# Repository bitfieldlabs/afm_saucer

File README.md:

# :flying_saucer: An RGB Attack from Mars Pinball Saucer PCB Replacement
As the title suggests this is drop in replacement for your Attack from Mars pinball saucer PCB. The large one.

No additional components or connections required!

As a bonus you get nice RGB colors!

See a video of the saucer in action: https://vimeo.com/777834938

## :jigsaw: Required Components

The BOM is [here](https://github.com/bitfieldlabs/afm_saucer/blob/master/afm_saucer_pcb/afm_saucer/afm_saucer_bom.csv).
 
## :page_facing_up: Instructions
Some instructions can be found in the [doc folder](https://github.com/bitfieldlabs/afm_saucer/tree/master/doc).

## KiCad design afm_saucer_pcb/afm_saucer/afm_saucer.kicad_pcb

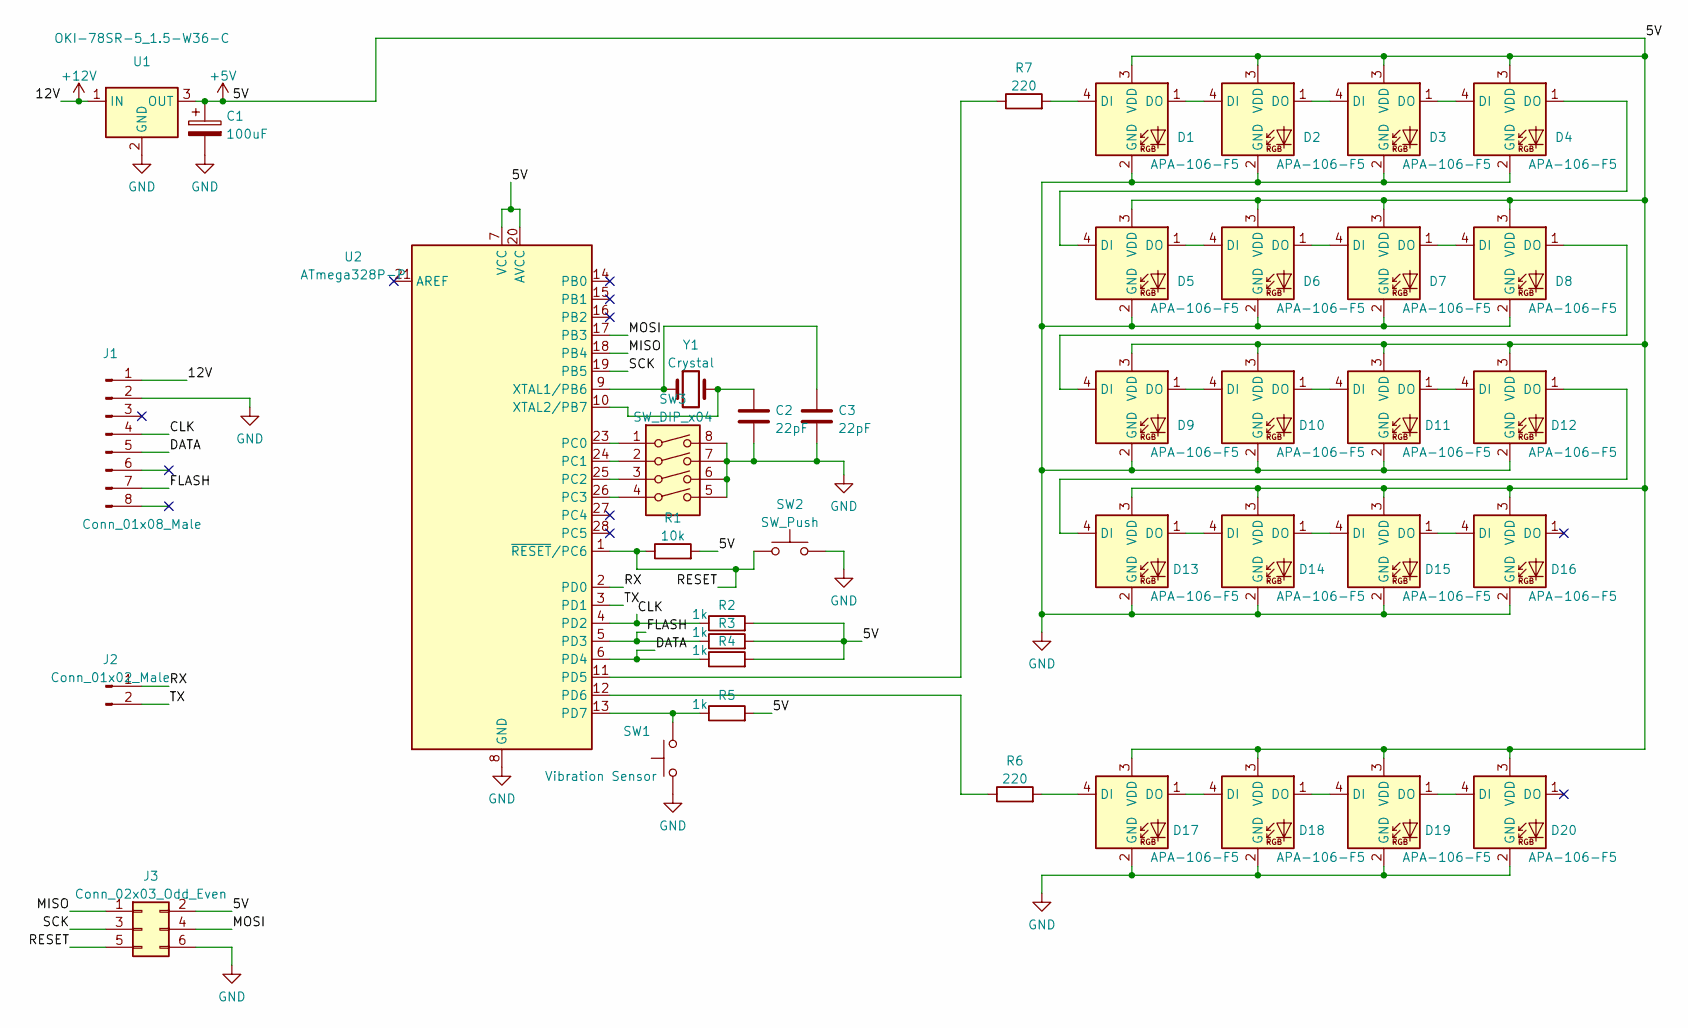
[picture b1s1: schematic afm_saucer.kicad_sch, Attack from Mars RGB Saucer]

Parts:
C1: 100uF; CP_Axial_L21.0mm_D8.0mm_P28.00mm_Horizontal
C2, C3: 22pF; C_Disc_D7.5mm_W5.0mm_P7.50mm
D1, D2, D3, D4, D5, D6, D7, D8, D9, D10, D11, D12, D13, D14, D15, D16, D17, D18, D19, D20: APA-106-F5; LED_D5.0mm-4_RGB
J1: Conn_01x08_Male; PinHeader_1x08_P2.54mm_Horizontal
J2: Conn_01x02_Male; PinHeader_1x02_P2.54mm_Vertical
J3: Conn_02x03_Odd_Even; PinHeader_2x03_P2.54mm_Vertical
R1: 10k; R_Axial_DIN0207_L6.3mm_D2.5mm_P10.16mm_Horizontal
R2, R3, R4, R5: 1k; R_Axial_DIN0207_L6.3mm_D2.5mm_P10.16mm_Horizontal
R6, R7: 220; R_Axial_DIN0207_L6.3mm_D2.5mm_P10.16mm_Horizontal
SW1: Vibration Sensor; PinHeader_1x02_P2.54mm_Horizontal
SW2: SW_Push; SW_PUSH_6mm_H9.5mm
SW3: SW_DIP_x04; SW_DIP_SPSTx04_Slide_9.78x12.34mm_W7.62mm_P2.54mm
U1: OKI-78SR-5_1.5-W36-C; Converter_DCDC_Murata_OKI-78SR_Horizontal
U2: ATmega328P-P; DIP-28_W7.62mm
Y1: Crystal; Resonator-2Pin_W10.0mm_H5.0mm

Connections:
+5V: C1.1, D1.3 (VDD), D2.3 (VDD), D3.3 (VDD), D4.3 (VDD), D5.3 (VDD), D6.3 (VDD), D7.3 (VDD), D8.3 (VDD), D9.3 (VDD), D10.3 (VDD), D11.3 (VDD), D12.3 (VDD), D13.3 (VDD), D14.3 (VDD), D15.3 (VDD), D16.3 (VDD), D17.3 (VDD), D18.3 (VDD), D19.3 (VDD), D20.3 (VDD), J3.2, R1.2, R2.2, R3.2, R4.2, R5.2, U1.3 (OUT), U2.7 (VCC), U2.20 (AVCC)
+12V: J1.1, U1.1 (IN)
/CLK: J1.4, R2.1, U2.4 (PD2)
/DATA: J1.5, R4.1, U2.6 (PD4)
/FLASH: J1.7, R3.1, U2.5 (PD3)
/MISO: J3.1, U2.18 (PB4)
/MOSI: J3.4, U2.17 (PB3)
/RESET: J3.5, R1.1, SW2.1, U2.1 (~RESET/PC6)
/RX: J2.1, U2.2 (PD0)
/SCK: J3.3, U2.19 (PB5)
/TX: J2.2, U2.3 (PD1)
GND: C1.2, C2.2, C3.2, D1.2 (GND), D2.2 (GND), D3.2 (GND), D4.2 (GND), D5.2 (GND), D6.2 (GND), D7.2 (GND), D8.2 (GND), D9.2 (GND), D10.2 (GND), D11.2 (GND), D12.2 (GND), D13.2 (GND), D14.2 (GND), D15.2 (GND), D16.2 (GND), D17.2 (GND), D18.2 (GND), D19.2 (GND), D20.2 (GND), J1.2, J3.6, SW1.1, SW2.2, SW3.5, SW3.6, SW3.7, SW3.8, U1.2 (GND), U2.8 (GND), U2.22 (GND)
unnamed: C2.1, U2.10 (XTAL2/PB7), Y1.2
unnamed: C3.1, U2.9 (XTAL1/PB6), Y1.1
unnamed: D1.1 (DO), D2.4 (DI)
unnamed: D1.4 (DI), R7.2
unnamed: D3.1 (DO), D4.4 (DI)
unnamed: D2.1 (DO), D3.4 (DI)
unnamed: D4.1 (DO), D5.4 (DI)
unnamed: D5.1 (DO), D6.4 (DI)
unnamed: D7.1 (DO), D8.4 (DI)
unnamed: D6.1 (DO), D7.4 (DI)
unnamed: D8.1 (DO), D9.4 (DI)
unnamed: D9.1 (DO), D10.4 (DI)
unnamed: D11.1 (DO), D12.4 (DI)
unnamed: D10.1 (DO), D11.4 (DI)
unnamed: D12.1 (DO), D13.4 (DI)
unnamed: D13.1 (DO), D14.4 (DI)
unnamed: D15.1 (DO), D16.4 (DI)
unnamed: D14.1 (DO), D15.4 (DI)
unnamed: D17.4 (DI), R6.2
unnamed: D18.1 (DO), D19.4 (DI)
unnamed: D17.1 (DO), D18.4 (DI)
unnamed: D19.1 (DO), D20.4 (DI)
unnamed: R5.1, SW1.2, U2.13 (PD7)
unnamed: R6.1, U2.12 (PD6)
unnamed: R7.1, U2.11 (PD5)
unnamed: SW3.1, U2.23 (PC0)
unnamed: SW3.2, U2.24 (PC1)
unnamed: SW3.3, U2.25 (PC2)
unnamed: SW3.4, U2.26 (PC3)

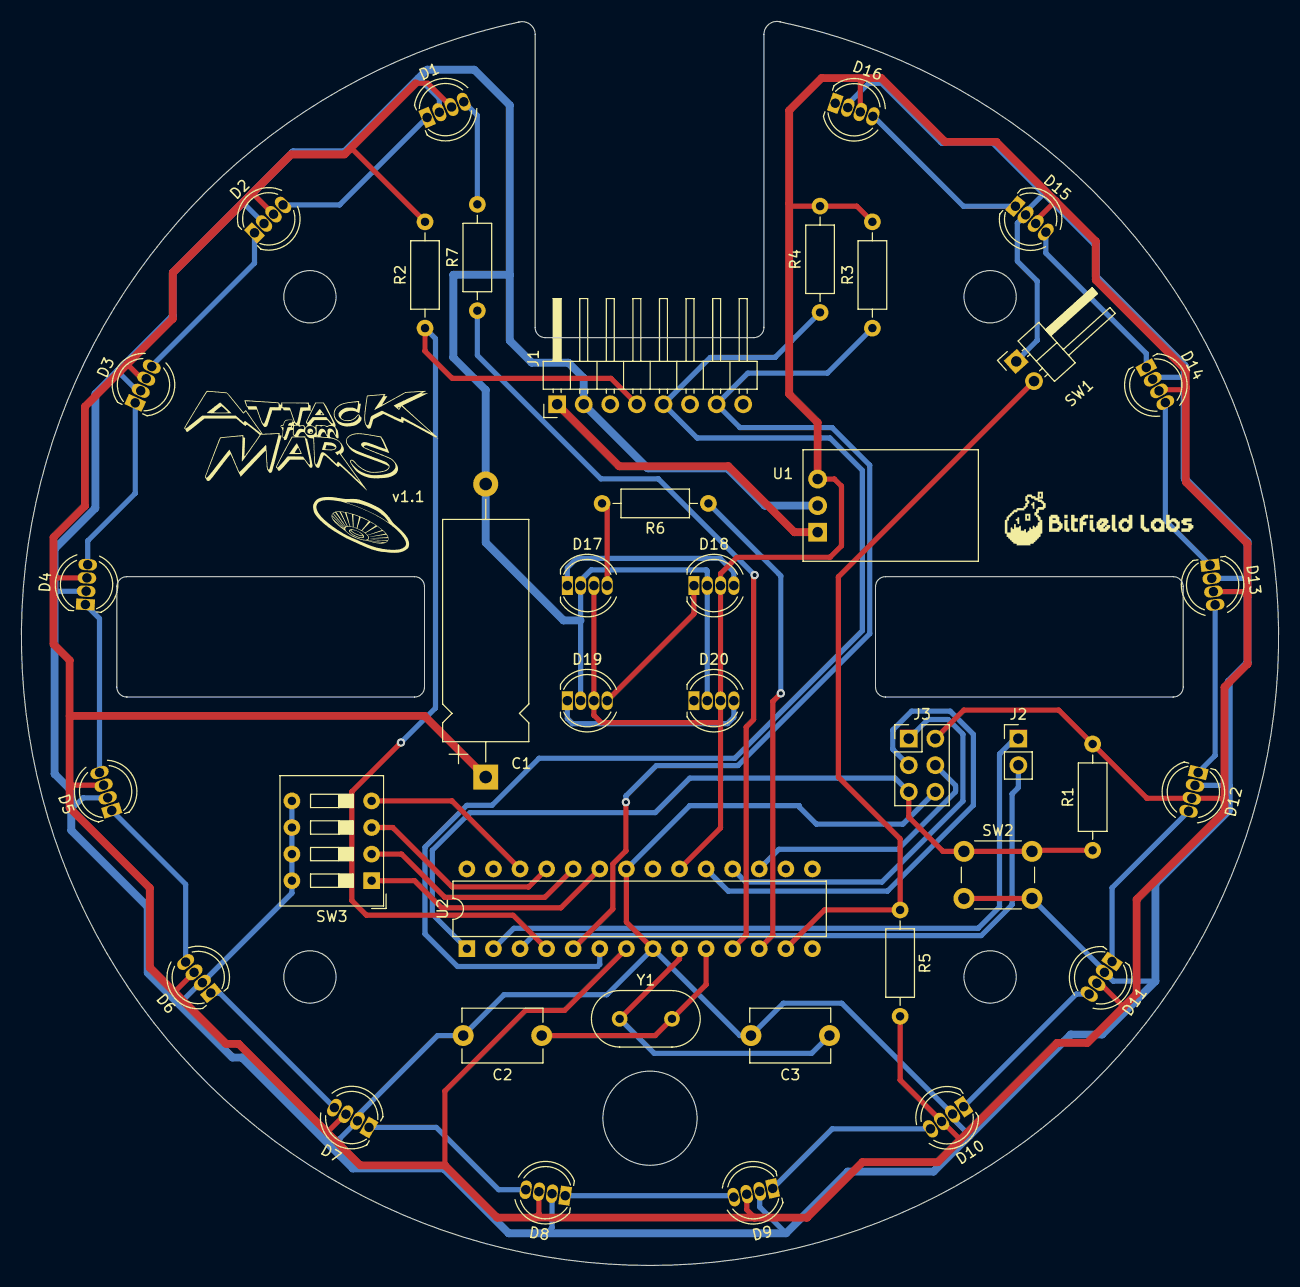
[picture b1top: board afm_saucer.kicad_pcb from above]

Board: 2 copper layers, 120.1 x 118.9 mm, 40 parts (0 on the bottom side), 41 nets.

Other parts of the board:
QR: QRCODE; afm_logo_s

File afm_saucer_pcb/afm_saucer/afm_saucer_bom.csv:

C1,100uF,Capacitor Axial L21.0mm D8.0mm P28.00mm,https://www.mouser.ch/ProductDetail/598-477TTA025M
"C2, C3",22pF,Capacitor Disc D7.5mm W5.0mm P7.50mm,https://www.mouser.ch/ProductDetail/810-CC45SL3JD220JYNA
D1-D20,APA-106-F5,LED D5.0mm RGB,https://www.aliexpress.com/item/32945500333.html?spm=a2g0o.o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
J1,Conn_01x08_Male,PinHeader 1x08 P2.54mm 90deg,https://www.mouser.ch/ProductDetail/538-22-05-7088
J2,Conn_01x02_Male,PinHeader 1x02_P2.54mm Vertical,
J3,Conn_02x03_Odd_Even,PinHeader 2x03 P2.54mm Vertical,
R1,10k,Resistor R_Axial L6.3mm D2.5mm P10.16mm,
"R2, R3, R4, R5",1k,Resistor R_Axial L6.3mm D2.5mm P10.16mm,
"R6, R7",220,Resistor R_Axial L6.3mm D2.5mm P10.16mm,
SW1,Vibration Sensor,Vibration Sensor Medium/Fast,https://www.mouser.ch/ProductDetail/485-2384
SW2,SW_Push,Push Button 6mm H9.5mm,
SW3,SW_DIP_x04,DIP  Switch x04 W7.62mm P2.54mm,
U1,OKI-78SR-5_1.5-W36-C,Converter DCDC_Murata OKI-78SR Horizontal,https://www.mouser.ch/ProductDetail/946-MEZD71202A-G
U2,ATmega328P-P,DIP-28 W7.62mm,
Y1,Crystal,Crystal 2Pin W10.0mm H5.0mm,https://www.mouser.ch/ProductDetail/449-LFXTAL027945BULK

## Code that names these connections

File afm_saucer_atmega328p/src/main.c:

/***********************************************************************
 *    _   _   _             _     __                                           
 *   /_\ | |_| |_ __ _  ___| | __/ _|_ __ ___  _ __ ___   /\/\   __ _ _ __ ___ 
 *  //_\\| __| __/ _` |/ __| |/ / |_| '__/ _ \| '_ ` _ \ /    \ / _` | '__/ __|
 * /  _  \ |_| || (_| | (__|   <|  _| | | (_) | | | | | / /\/\ \ (_| | |  \__ \
 * \_/ \_/\__|\__\__,_|\___|_|\_\_| |_|  \___/|_| |_| |_\/    \/\__,_|_|  |___/
 *
 *                              ____ ____ ___ 
 *                              |--< |__, |==]
 *
 *                      ____ ____ _  _ ____ ____ ____
 *                      ==== |--| |__| |___ |=== |--<
 *
 *  Copyright (c) 2022 bitfield labs
 * 
 ***********************************************************************
 *  This file is part of the Attack from Mars! RGB saucer project:
 *  https://github.com/bitfieldlabs/afm_saucer
 *
 *  The AfM RGB saucer is free software: you can redistribute it and/or
 *  modify it under the terms of the GNU Lesser General Public License as
 *  published by the Free Software Foundation, either version 3 of the
 *  License, or (at your option) any later version.
 *
 *  AfM RGB saucer is distributed in the hope that it will be useful,
 *  but WITHOUT ANY WARRANTY; without even the implied warranty of
 *  MERCHANTABILITY or FITNESS FOR A PARTICULAR PURPOSE.  See the
 *  GNU Lesser General Public License for more details.
 *
 *  You should have received a copy of the GNU Lesser General Public
 *  License along with afterglow.
 *  If not, see <http://www.gnu.org/licenses/>.
 ***********************************************************************/

#include <avr/io.h>
#include <avr/interrupt.h>
#include <avr/eeprom.h>
#include <util/delay.h>
#include <stdlib.h>
#include <stdbool.h>
#include "modes.h"


//------------------------------------------------------------------------------
// definitions

#define LED_UPDATE_INT 20                   // LED update interval [ms]
#define FLASH_CONS_CHECK 1                  // number of consecutive flash line checks in LED_UPDATE_INT interval required for flash triggering


//------------------------------------------------------------------------------
// global variables

static volatile uint16_t svLEDState = 0xffff;    // status for all 16 LEDs
static volatile bool svFlashState = false;       // flasher status
static volatile bool svShakerState = false;      // shaker status
static volatile uint16_t svFlashCounter = 0;     // consecutive passed flash line checks counter


//------------------------------------------------------------------------------
int main(void)
{
    // setup
    DDRD = 0b01100010;                      // all inputs except pins PD1, PD5, PD6
    DDRC = 0b00000000;                      // config DIPs on PC0-PC3
    PORTC |= 0b00001111;                    // enable DIP switch pullups
    EICRA |= (1 << ISC00) | (1 << ISC01);   // trigger INT0 on rising edge
    EIMSK |= (1 << INT0);                   // turn on INT0
    EICRA |= (1 << ISC11);                  // trigger INT1 on falling edge
    EIMSK |= (1 << INT1);                   // turn on INT1
    PCICR |= (1 << PCIE2);                  // enable pin interrupt
    PCMSK2 |= (1 << PCINT23);               // pin change interrupt on PD7 (PCINT23)

    // seed the random number generator
    uint32_t seed = eeprom_read_dword((uint32_t*)0);
    srand(seed);
    eeprom_write_dword((uint32_t*)0, rand());

    // enable interrupts
    sei();

    // to infinity and beyond
    while (true)
    {
        // update the LED state upon change
        updateLEDState(svLEDState);
        if (svFlashState)
        {
            // noise filtering: make sure the flash line is still kept low for at
            // least FLASH_CONS_CHECK consecutive checks
            if (!(PIND & 0b00001000))
            {
                svFlashCounter++;
                if (svFlashCounter >= FLASH_CONS_CHECK)
                {
                    triggerFlasher();
                    svFlashCounter = 0;
                    svFlashState = false;
                }
            }
            else
            {
                svFlashCounter = 0;
                svFlashState = false;
            }
        }
        if (svShakerState)
        {
            triggerShaker();
            svShakerState = false;
        }

        // update all LEDs
        updateLEDs();

        // wait a bit
        _delay_ms(LED_UPDATE_INT);
    }
    return 0;
}

//------------------------------------------------------------------------------
// LED data interrupt
ISR(INT0_vect)
{
    // shift new value into LED status
    svLEDState <<= 1;
    *((uint8_t*)&svLEDState) |= ((PIND >> 4) & 0x01);
}

//------------------------------------------------------------------------------
// flasher interrupt
ISR(INT1_vect)
{
    svFlashState = true;
}

//------------------------------------------------------------------------------
// shaker interrupt
ISR(PCINT2_vect)
{
    svShakerState = true;
}

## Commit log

2022-12-04 tut was
2022-12-04 tuning
2022-12-04 BetterShaker(TM)
2022-12-04 animations
2022-12-04 Preparing for modes
2022-12-04 Cleanup
2022-12-04 Meh bessere Code
2022-12-04 Shake it, baby!
2022-12-04 tut no meh
2022-12-04 Nice pictures
2022-12-04 More pictures
2022-12-09 Added BOM
2022-12-09 PCB v1.1
2022-12-10 More patterns
2022-12-16 Dummy patterns
2022-12-16 LGPL
2022-12-24 Pattern work
2022-12-29 More pattern work
2022-12-30 Random pattern 0
2022-12-30 Better shaking
2022-12-30 Revert bad commit
2022-12-30 Last pattern
2022-12-30 Jingle all the way
2022-12-31 Fixed jingl
2022-12-31 Fixed test mode
2022-12-31 Fine tuning
2022-12-31 Assmebly docu
2022-12-31 More documentation
2023-05-08 Added missing files
2025-04-27 Flasher interrupt noise filtering
